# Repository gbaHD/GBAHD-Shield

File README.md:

# gbaHD Shield
This is a shield for the [gbaHD project](https://github.com/zwenergy/gbaHD).  

# What is the gbaHD Shield?
The gbaHD Shield is an easy solution to interface with the Spartan Edge Accelerator Board used for the gbaHD Project and the GBA / GBA-SP itself.

It has the following features.
- Connects via female headers to the Edge board (shield)
- Has a FFC 40 pin connector for OGBA LCD connector. Need Type-B Cable (Reverse) vvv=======^^^
- Has a FFC 32 pin connector for OGBA LCD connector. Need Type-B Cable (Reverse) vvv=======^^^
- Has a FFC 34 pin connector for GBA-SP LCD connector. Need Type-A Cable (Direct) vvv=======vvv
- Has a FFC 16 pin connector for controls with a wire up board. Need Type-B Cable (Reverse) vvv=======^^^
- Has a ATMEGA328p / ATMEGA168p / ATMEGA88p for using a SNES connector to control the GBA.
- Has a high-side switch for GBA power controls (IGR).
- Optional Flex-Cable to solder on the the CPU of the GBA and the GBASP
- Unused ATMEGA-Pins are broken out as testpoints on the top and bottom side for future features.

In cooperation with bbsan the featureset of the Shield has been expanded.
The new features are:
- Update of the ATMEGA Firmwre over the ESP32
- Bluetooth-Controller Support
- WebUI
- OTA-Update of the ESP32, ATMEGA and Bitstreams over the WebUI
- Bitstream selection (720p / 1080p) in the WebUI

## Special Thanks
- @zwenergy0 for the gbaHD-Project itself
- @bbsan2k for all the hard work with the ESP32-Side
- @ManCloud for the Shield design itself
- @jotheripper for the awesome cases (https://www.prusaprinters.org/social/170041-jotheripper/about)
- @ricardoquesada for the BluePad-Implementation (https://github.com/ricardoquesada/bluepad32)

## Contributing
If you wish to contribute, see something wrong or want to add a feature please make a pull request or leave an issue!

## BOM
|Reference	|Value    |
|---------	|--------						|
|C1,C3	|100nF - 0805|
|C2	|22u - 0805|
|C4	|47uF - 0805|
|R1	|2.2k - 0805|
|R2,R7,R6	|1k - 0805|
|R3,R4,R8	|10K - 0805|
|R5	|500 - 0805|
|D1	|LED RED - 0805|
|D2	|LED GREEN - 0805|
|U1	|AZ1117R-ADJ - SOT-89-3|
|U2,U3	|74HC595 - SOIC-16|
|U4	|SNES_7PIN|
|U5	|ATmega328P-AU|
|U5-Alternative	|ATmega168P-AU|
|U5-Alternative-Alternative	|ATmega88PA-AU|
|Q1	|SI2301CDS-T1-GE3 - SOT-23|
|Q2,Q3	|2N7002 - SOT-23|
|SW1	|XKB-TS-1185EC-C-D-B|
|J2			|32Pin 0.5 Pitch, bottom contacts|
|J3			|34Pin 0.5 Pitch, bottom contacts|
|J4			|16Pin 0.5 Pitch, bottom contacts|
|J5			|40Pin 0.5 Pitch, bottom contacts|
|J6	|PinHeader 1x6 2.54mm|
|J7,J9	|PinHeader 1x8 2.54mm|
|J8,J10	|PinHeader 1x10 2.54mm|

## Images

Breakout-Board for the OGBA

Breakout-Board for the GBA-SP

Flex-Cable for the GBA

Flex-Cable for the GBA-SP

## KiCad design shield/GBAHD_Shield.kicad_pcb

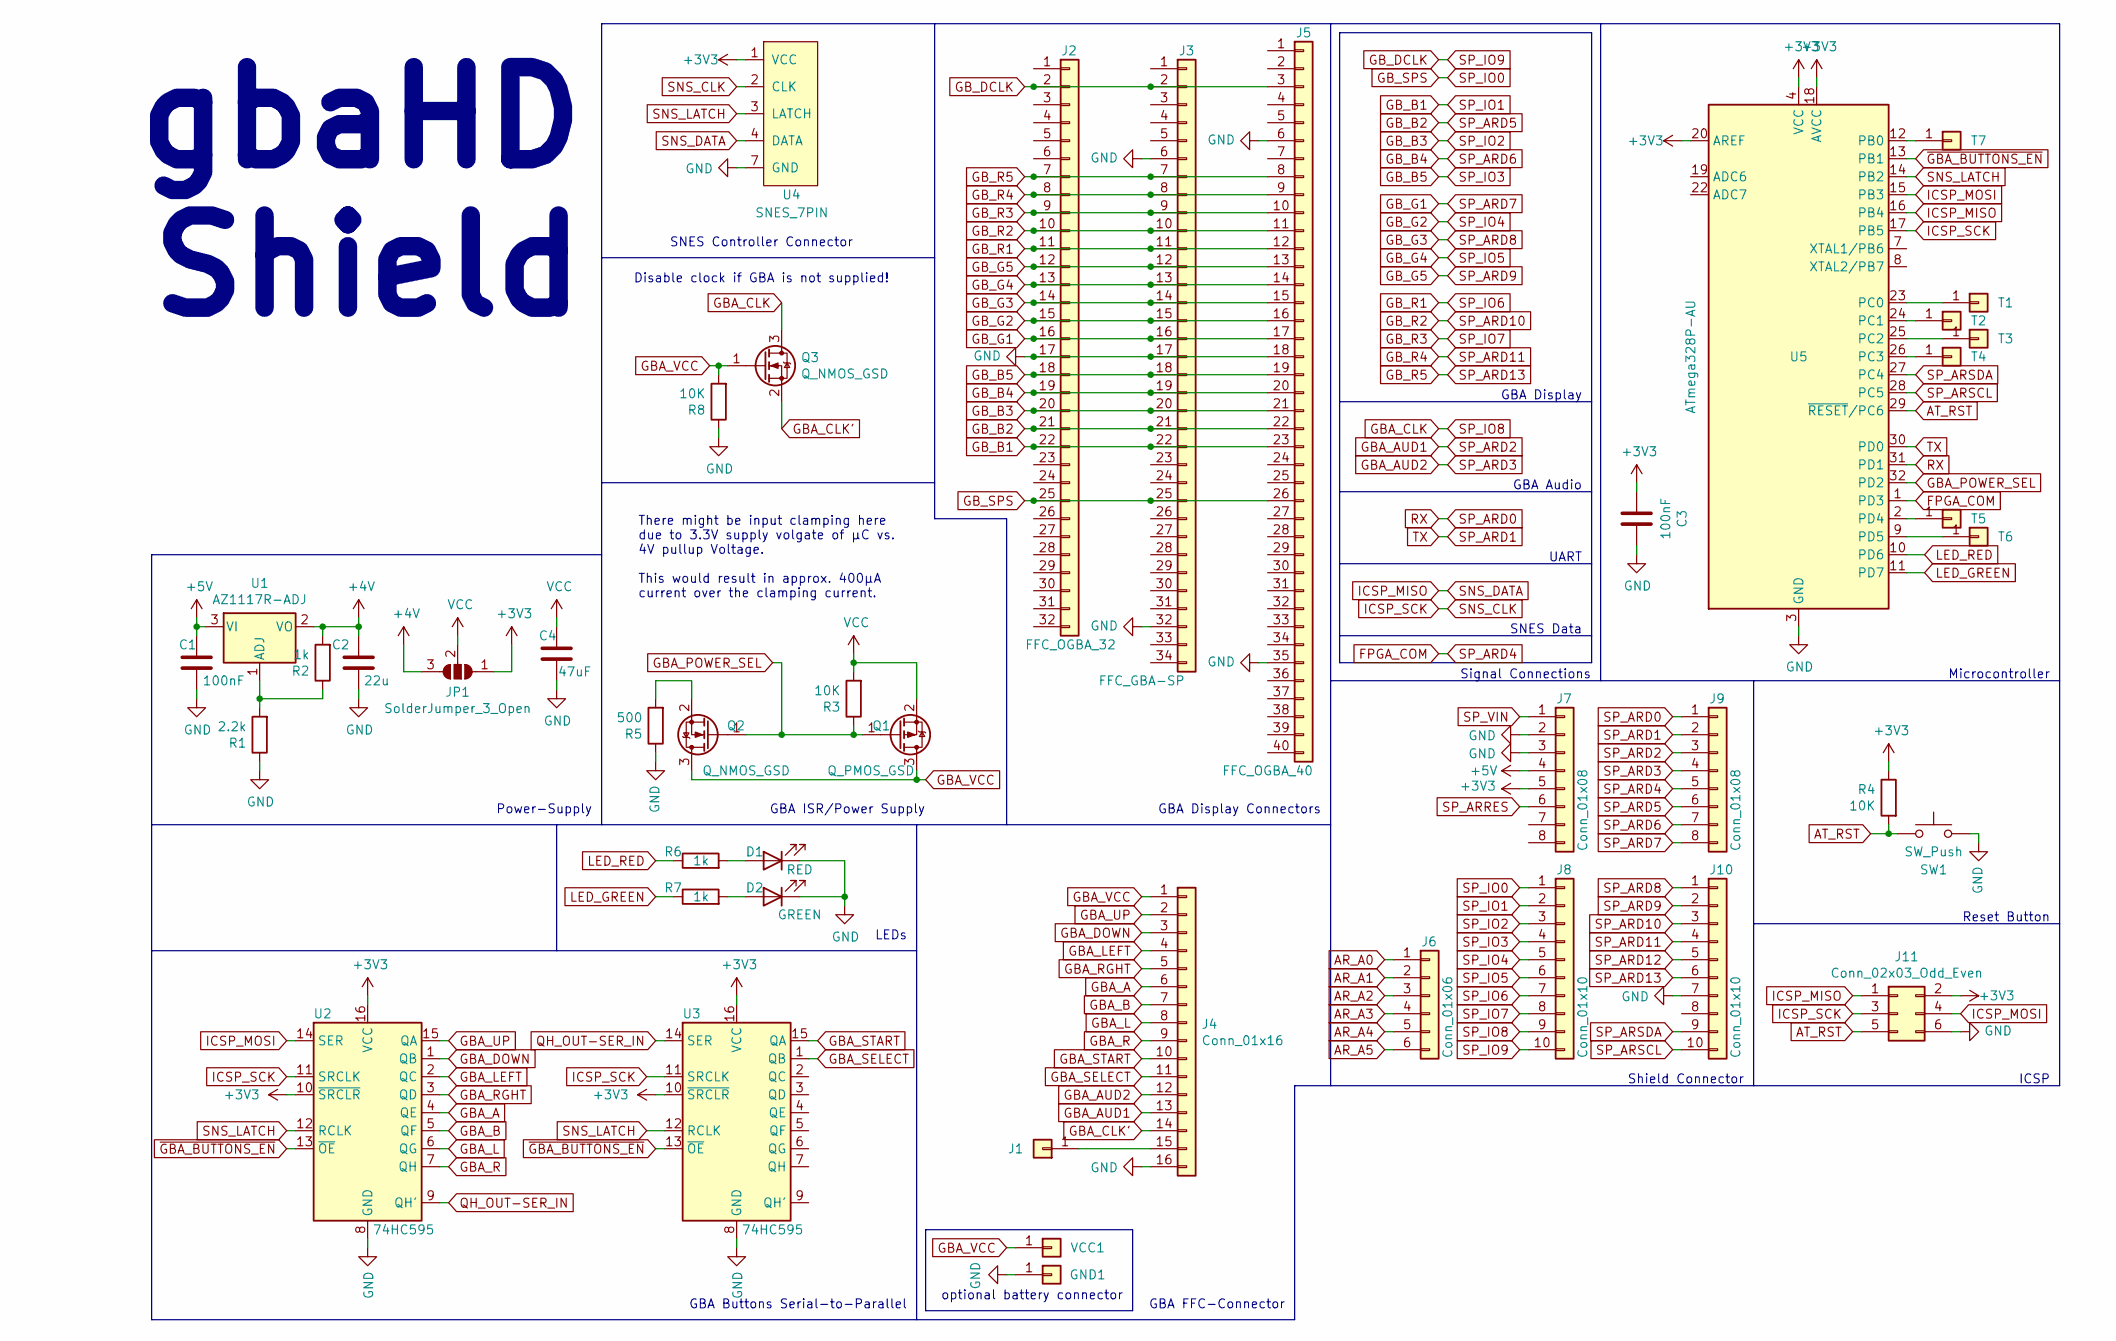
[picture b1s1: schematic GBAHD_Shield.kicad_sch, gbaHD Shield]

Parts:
C1, C3: 100nF; C_0805_2012Metric_Pad1.18x1.45mm_HandSolder
C2: 22u; C_0805_2012Metric_Pad1.18x1.45mm_HandSolder
C4: 47uF; C_0805_2012Metric_Pad1.18x1.45mm_HandSolder
D1: RED; LED_0805_2012Metric_Pad1.15x1.40mm_HandSolder
D2: GREEN; LED_0805_2012Metric_Pad1.15x1.40mm_HandSolder
GND1: Conn_01x01; TestPoint_Pad_1.5x1.5mm
J1: Conn_01x01; TestPoint_Pad_1.5x1.5mm
J2: FFC_OGBA_32; TE_3-1734839-2_1x32-1MP_P0.5mm_Horizontal
J3: FFC_GBA-SP; TE_3-1734839-4_1x34-1MP_P0.5mm_Horizontal
J4: Conn_01x16; TE_1-1734839-6_1x16-1MP_P0.5mm_Horizontal
J5: FFC_OGBA_40; TE_4-1734839-0_1x40-1MP_P0.5mm_Horizontal
J6: Conn_01x06; PinHeader_1x06_P2.54mm_Vertical
J7, J9: Conn_01x08; PinHeader_1x08_P2.54mm_Vertical
J8, J10: Conn_01x10; PinHeader_1x10_P2.54mm_Vertical
J11: Conn_02x03_Odd_Even; PinHeader_2x03_P2.54mm_Vertical
JP1: SolderJumper_3_Open; SolderJumper-3_P1.3mm_Open_Pad1.0x1.5mm_NumberLabels
Q1: Q_PMOS_GSD; SOT-23
Q2, Q3: Q_NMOS_GSD; SOT-23
R1: 2.2k; R_0805_2012Metric_Pad1.20x1.40mm_HandSolder
R2, R6, R7: 1k; R_0805_2012Metric_Pad1.20x1.40mm_HandSolder
R3, R4, R8: 10K; R_0805_2012Metric_Pad1.20x1.40mm_HandSolder
R5: 500; R_0805_2012Metric_Pad1.20x1.40mm_HandSolder
SW1: SW_Push; SW_Push_1P1T_NO_CK_KMR2
T1, T2, T3, T4, T5, T6, T7: Conn_01x01; TestPoint_Pad_D1.5mm
U1: AZ1117R-ADJ; SOT-89-3
U2, U3: 74HC595; SOIC-16_3.9x9.9mm_P1.27mm
U4: SNES_7PIN
U5: ATmega328P-AU; TQFP-32_7x7mm_P0.8mm
VCC1: Conn_01x01; TestPoint_Pad_1.5x1.5mm

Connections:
+3V3: C3.2, J7.5, J11.2, JP1.1 (A), R4.1, U2.10 (~SRCLR), U2.16 (VCC), U3.10 (~SRCLR), U3.16 (VCC), U4.1 (VCC), U5.4 (VCC), U5.6 (VCC), U5.18 (AVCC), U5.20 (AREF)
+4V: C2.2, JP1.3 (B), R2.2, U1.2 (VO)
+5V: C1.2, J7.4, U1.3 (VI)
AR_A0: J6.1
AR_A1: J6.2
AR_A2: J6.3
AR_A3: J6.4
AR_A4: J6.5
AR_A5: J6.6
AT_RST: J11.5, R4.2, SW1.1, U5.29 (~RESET/PC6)
FPGA_COM: J9.5, U5.1 (PD3)
GBA_A: J4.6, U2.4 (QE)
GBA_AUD1: J4.13, J9.3
GBA_AUD2: J4.12, J9.4
GBA_B: J4.7, U2.5 (QF)
GBA_CLK: J8.9, Q3.3 (D)
GBA_CLK': J4.14, Q3.2 (S)
GBA_DOWN: J4.3, U2.1 (QB)
GBA_L: J4.8, U2.6 (QG)
GBA_LEFT: J4.4, U2.2 (QC)
GBA_POWER_SEL: Q1.1 (G), Q2.1 (G), R3.1, U5.32 (PD2)
GBA_R: J4.9, U2.7 (QH)
GBA_RGHT: J4.5, U2.3 (QD)
GBA_SELECT: J4.11, U3.1 (QB)
GBA_START: J4.10, U3.15 (QA)
GBA_UP: J4.2, U2.15 (QA)
GBA_VCC: J4.1, Q1.3 (D), Q2.3 (D), Q3.1 (G), R8.2, VCC1.1
GB_B1: J2.22, J3.22, J5.23, J8.2
GB_B2: J2.21, J3.21, J5.22, J9.6
GB_B3: J2.20, J3.20, J5.21, J8.3
GB_B4: J2.19, J3.19, J5.20, J9.7
GB_B5: J2.18, J3.18, J5.19, J8.4
GB_DCLK: J2.2, J3.2, J5.3, J8.10
GB_G1: J2.16, J3.16, J5.17, J9.8
GB_G2: J2.15, J3.15, J5.16, J8.5
GB_G3: J2.14, J3.14, J5.15, J10.1
GB_G4: J2.13, J3.13, J5.14, J8.6
GB_G5: J2.12, J3.12, J5.13, J10.2
GB_R1: J2.11, J3.11, J5.12, J8.7
GB_R2: J2.10, J3.10, J5.11, J10.3
GB_R3: J2.9, J3.9, J5.10, J8.8
GB_R4: J2.8, J3.8, J5.9, J10.4
GB_R5: J2.7, J3.7, J5.8, J10.6
GB_SPS: J2.25, J3.25, J5.26, J8.1
GND: C1.1, C2.1, C3.1, C4.1, D1.1 (K), D2.1 (K), GND1.1, J2.17, J3.6, J3.17, J3.32, J4.16, J5.6, J5.18, J5.35, J7.2, J7.3, J10.7, J11.6, R1.1, R5.1, R8.1, SW1.2, U2.8 (GND), U3.8 (GND), U4.7 (GND), U5.3 (GND), U5.5 (GND), U5.21 (GND)
ICSP_MISO: J11.1, U4.4 (DATA), U5.16 (PB4)
ICSP_MOSI: J11.4, U2.14 (SER), U5.15 (PB3)
ICSP_SCK: J11.3, U2.11 (SRCLK), U3.11 (SRCLK), U4.2 (CLK), U5.17 (PB5)
LED_GREEN: R7.1, U5.11 (PD7)
LED_RED: R6.1, U5.10 (PD6)
unnamed: D1.2 (A), R6.2
unnamed: D2.2 (A), R7.2
unnamed: J1.1, J4.15
unnamed: Q2.2 (S), R5.2
unnamed: R1.2, R2.1, U1.1 (ADJ)
unnamed: T1.1, U5.23 (PC0)
unnamed: T2.1, U5.24 (PC1)
unnamed: T3.1, U5.25 (PC2)
unnamed: T4.1, U5.26 (PC3)
unnamed: T5.1, U5.2 (PD4)
unnamed: T6.1, U5.9 (PD5)
unnamed: T7.1, U5.12 (PB0)
QH_OUT-SER_IN: U2.9 (QH'), U3.14 (SER)
RX: J9.1, U5.31 (PD1)
SNS_LATCH: U2.12 (RCLK), U3.12 (RCLK), U4.3 (LATCH), U5.14 (PB2)
SP_ARD1: J9.2, U5.30 (PD0)
SP_ARD12: J10.5
SP_ARRES: J7.6
SP_ARSCL: J10.10, U5.28 (PC5)
SP_ARSDA: J10.9, U5.27 (PC4)
SP_VIN: J7.1
VCC: C4.2, JP1.2 (C), Q1.2 (S), R3.2
~GBA_BUTTONS_EN: U2.13 (~OE), U3.13 (~OE), U5.13 (PB1)

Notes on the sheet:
ICSP
GBA Buttons Serial-to-Parallel
GBA FFC-Connector
GBA ISR/Power Supply
SNES Data
optional battery connector
There might be input clamping here due to 3.3V supply volgate of µC vs. 4V pullup Voltage. This would result in approx. 400µA current over the clamping current.
Microcontroller
GBA Display Connectors
Shield Connector
gbaHD Shield
UART
LEDs
Power-Supply
Disable clock if GBA is not supplied!
SNES Controller Connector
Reset Button
Signal Connections
GBA Display
GBA Audio

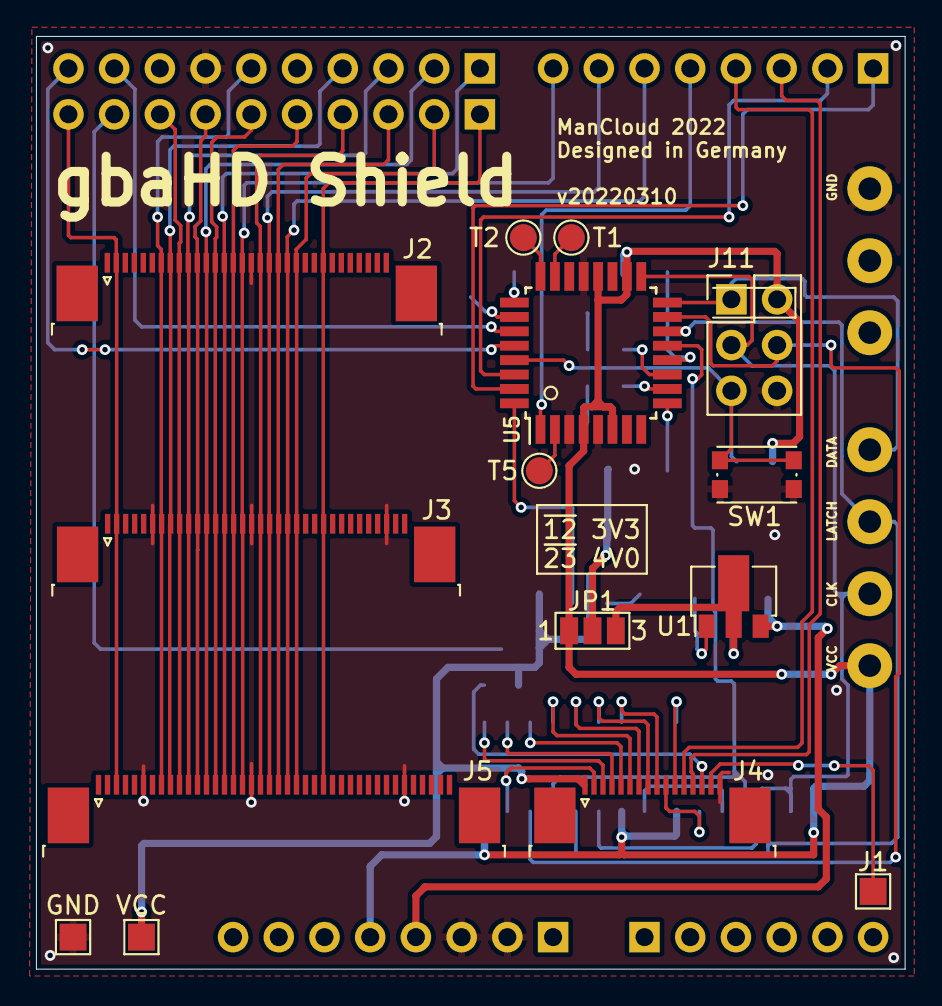
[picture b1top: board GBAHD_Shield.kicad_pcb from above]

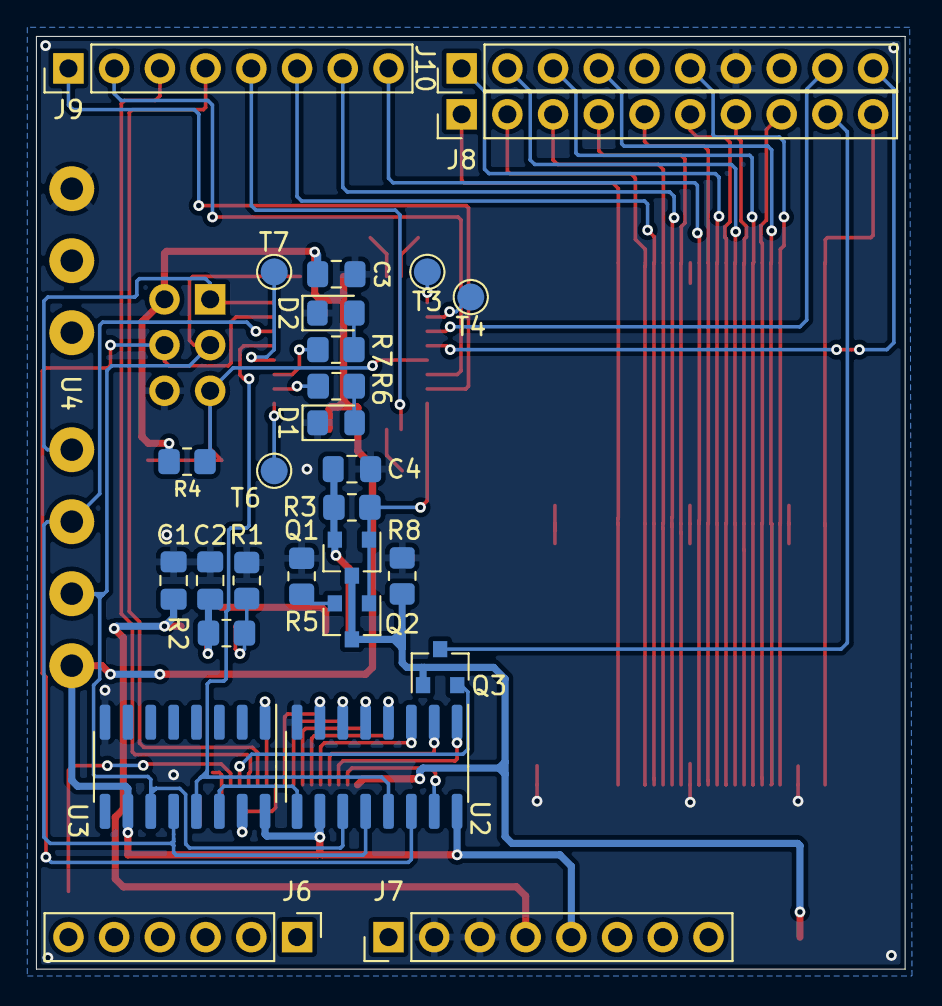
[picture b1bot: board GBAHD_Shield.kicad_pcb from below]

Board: 2 copper layers, 48.3 x 51.8 mm, 44 parts (29 on the bottom side), 64 nets.

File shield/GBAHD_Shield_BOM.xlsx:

ID | Part | Outline | Qty. | Value | Reference | LCSC Part Number | Note
1 | C1,C3 | C_0805_2012Metric_Pad1.18x1.45mm_HandSolder | 2 | 100nF |  | C519981
2 | C2 | C_0805_2012Metric_Pad1.18x1.45mm_HandSolder | 1 | 22u |  | C109314
3 | J11 | PinHeader_2x03_P2.54mm_Vertical | 1 | Conn_02x03_Odd_Even |  | C65114
4 | J2 | TE_3-1734839-2_1x32-1MP_P0.5mm_Horizontal | 1 | FFC_OGBA_32 | JUSHUO AFC07-S32FCC-00 | C11061
5 | J3 | TE_3-1734839-4_1x34-1MP_P0.5mm_Horizontal | 1 | FFC_GBA-SP | JUSHUO AFC07-S34FCC-00 | C262221
6 | J4 | TE_1-1734839-6_1x16-1MP_P0.5mm_Horizontal | 1 | Conn_01x16 | JUSHUO AFC07-S16FCC-00 | C11053
7 | J5 | TE_4-1734839-0_1x40-1MP_P0.5mm_Horizontal | 1 | FFC_OGBA_40 | JUSHUO AFC07-S40FCC-00 | C11062
8 | J6 | PinHeader_1x06_P2.54mm_Vertical | 1 | Conn_01x06 |  | C40877
9 | J8,J10 | PinHeader_1x10_P2.54mm_Vertical | 2 | Conn_01x10 |  | C35445
10 | J9,J7 | PinHeader_1x08_P2.54mm_Vertical | 2 | Conn_01x08 |  | C27438
11 | Q1 | SOT-23 | 1 | Q_PMOS_GSD | SI2301DS | C10487
12 | R1 | R_0805_2012Metric_Pad1.20x1.40mm_HandSolder | 1 | 2.2k |  | C228697
13 | R2 | R_0805_2012Metric_Pad1.20x1.40mm_HandSolder | 1 | 1k |  | C140870
14 | R4,R3 | R_0805_2012Metric_Pad1.20x1.40mm_HandSolder | 2 | 10K |  | C84376
15 | SW1 | SW_Push_1P1T_NO_CK_KMR2 | 1 | SW_Push | TS-1185EC-C-D-B | C318893
16 | U1 | SOT-89-3 | 1 | LM1117F-ADJ |  | C126021
17 | U2,U3 | SOIC-16_3.9x9.9mm_P1.27mm | 2 | 74HC595 |  | C5947
18 | U4 | SNES_7PIN | 1 | SNES_7PIN |  |  | Available on aliexpress - make sure you choose the right angle one (180 degrees) | https://de.aliexpress.com/item/32828768824.html?spm=a2g0o.pr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
19 | U5 | TQFP-32_7x7mm_P0.8mm | 1 | ATmega328P-AU |  | C14877
20 |  |  | 2 |  | Pin Headers 1*40 Pin |  | Available on aliexpress - make sure you choose the right angle one (180 degrees) | https://de.aliexpress.com/item/32993182990.html?spm=a2g0o.pr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
 |  | Flexcable 40 Pin | 1 |  | 0.020"(0.50mm) 40 Opposite Side FFC/FPC Connectors RoHS | C11100 | The flex is a bit long, but you can fold it to fit. LCSC has no shorter ones
 |  | Flexcable 16 Pin | 1 |  | 0.020"(0.50mm) 16 Opposite Side FFC/FPC Connectors RoHS | C11114 | The flex is a bit long, but you can fold it to fit. LCSC has no shorter ones
 |  | Flexcable 32 Pin | 1 |  | 0.020"(0.50mm) 32 Opposite Side FFC/FPC Connectors RoHS | C11118 | The flex is a bit long, but you can fold it to fit. LCSC has no shorter ones
 |  | Flexcable 34 Pin | 1 |  | 0.020"(0.50mm) 32 Same Side FFC/FPC Connectors RoHS |  | Not available on LCSC, try ordering on ebay, aliexpress e.g. | https://de.aliexpress.com/item/1005002259855390.html?spm=a2g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

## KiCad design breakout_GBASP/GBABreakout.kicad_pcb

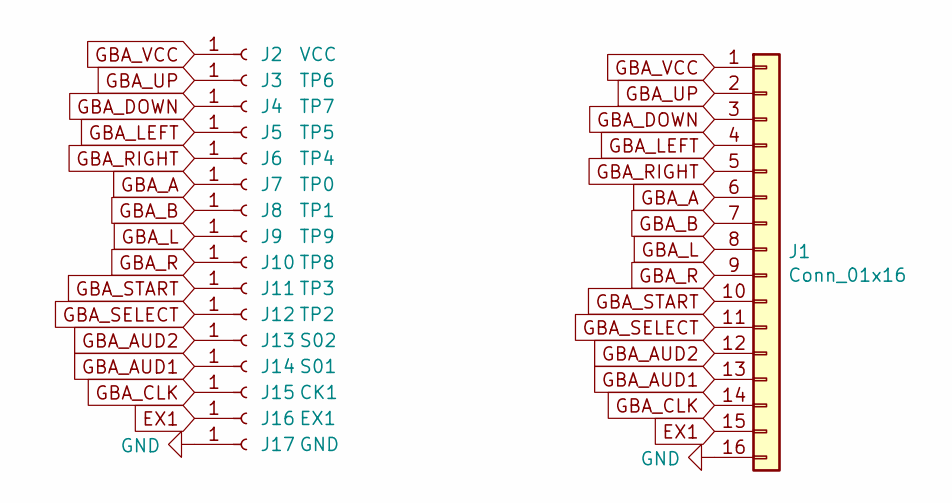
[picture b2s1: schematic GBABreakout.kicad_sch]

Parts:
J1: Conn_01x16; TE_1-1734839-6_1x16-1MP_P0.5mm_Horizontal
J2: VCC; SOLDER_PAD
J3: TP6; SOLDER_PAD
J4: TP7; SOLDER_PAD
J5: TP5; SOLDER_PAD
J6: TP4; SOLDER_PAD
J7: TP0; SOLDER_PAD
J8: TP1; SOLDER_PAD
J9: TP9; SOLDER_PAD
J10: TP8; SOLDER_PAD
J11: TP3; SOLDER_PAD
J12: TP2; SOLDER_PAD
J13: S02; SOLDER_PAD
J14: S01; SOLDER_PAD
J15: CK1; SOLDER_PAD
J16: EX1; SOLDER_PAD
J17: GND; SOLDER_PAD

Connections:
EX1: J1.15, J16.1
GBA_A: J1.6, J7.1
GBA_AUD1: J1.13, J14.1
GBA_AUD2: J1.12, J13.1
GBA_B: J1.7, J8.1
GBA_CLK: J1.14, J15.1
GBA_DOWN: J1.3, J4.1
GBA_L: J1.8, J9.1
GBA_LEFT: J1.4, J5.1
GBA_R: J1.9, J10.1
GBA_RIGHT: J1.5, J6.1
GBA_SELECT: J1.11, J12.1
GBA_START: J1.10, J11.1
GBA_UP: J1.2, J3.1
GBA_VCC: J1.1, J2.1
GND: J1.16, J17.1

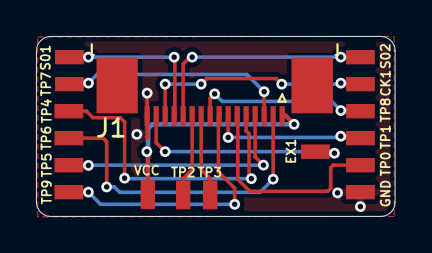
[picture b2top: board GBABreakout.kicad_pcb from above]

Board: 2 copper layers, 19.9 x 10.0 mm, 17 parts (0 on the bottom side), 16 nets.

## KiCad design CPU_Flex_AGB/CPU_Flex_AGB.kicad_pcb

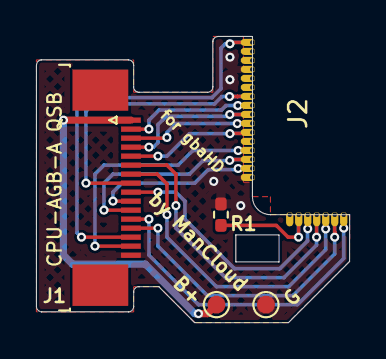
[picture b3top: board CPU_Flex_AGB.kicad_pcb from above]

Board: 2 copper layers, 17.4 x 15.9 mm, 5 parts (0 on the bottom side), 17 nets.

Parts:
B+: BAT+; TestPoint_Pad_D1.0mm
G: GND; TestPoint_Pad_D1.0mm
J1: Conn_01x16; TE_1-1734839-6_1x16-1MP_P0.5mm_Horizontal
J2: CPU_AGB_A_Interface; CPU_AGB_A_INTERFACE
R1: 100k; R_0402_1005Metric_Pad0.72x0.64mm_HandSolder

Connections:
GND: G.1, J1.16, J2.116 (GND), J2.128 (GND), R1.1
unnamed: J1.2, J2.120 (TP6)
unnamed: J1.3, J2.122 (TP7)
unnamed: J1.4, J2.121 (TP5)
unnamed: J1.5, J2.123 (TP4)
unnamed: J1.6, J2.4 (TP0)
unnamed: J1.7, J2.5 (TP1)
unnamed: J1.8, J2.119 (TP9)
unnamed: J1.9, J2.3 (TP8)
unnamed: J1.10, J2.127 (TP3)
unnamed: J1.11, J2.126 (TP2)
unnamed: J1.12, J2.7 (S02)
unnamed: J1.13, J2.6 (S01)
unnamed: J1.14, J2.113 (CK1)
unnamed: J1.15, J2.125 (RESET)
unnamed: J2.2 (IN35), R1.2
VCC: B+.1, J1.1

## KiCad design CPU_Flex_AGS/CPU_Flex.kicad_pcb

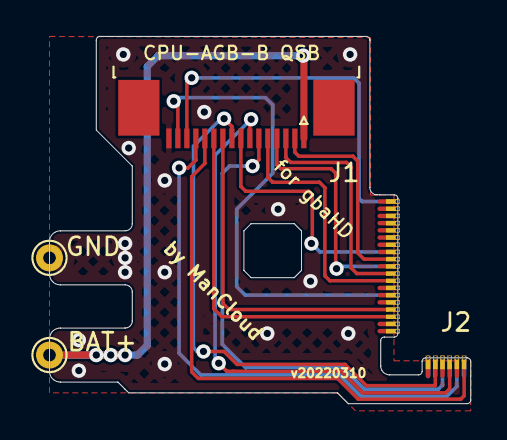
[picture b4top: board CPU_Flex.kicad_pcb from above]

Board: 2 copper layers, 23.4 x 20.4 mm, 4 parts (0 on the bottom side), 16 nets.

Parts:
BAT+: Conn_01x01; TestPoint_THTPad_D1.5mm_Drill0.7mm
GND: Conn_01x01; TestPoint_THTPad_D1.5mm_Drill0.7mm
J1: Conn_01x16; TE_1-1734839-6_1x16-1MP_P0.5mm_Horizontal
J2: CPU AGB B Interface; CPU_AGB_B_Interface

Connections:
/GBA_A: J1.6, J2.3 (TP0)
/GBA_AUD_L: J1.12, J2.6 (S02)
/GBA_AUD_R: J1.13, J2.5 (S01)
/GBA_B: J1.7, J2.4 (TP1)
/GBA_CLK: J1.14, J2.138 (CK1)
/GBA_DOWN: J1.3, J2.148 (TP7)
/GBA_L: J1.8, J2.145 (TP9)
/GBA_LEFT: J1.4, J2.147 (TP5)
/GBA_R: J1.9, J2.2 (TP8)
/GBA_RESET: J1.15, J2.151 (RESET)
/GBA_RIGHT: J1.5, J2.149 (TP4)
/GBA_SELECT: J1.11, J2.154 (TP2)
/GBA_START: J1.10, J2.153 (TP3)
/GBA_UP: J1.2, J2.146 (TP6)
GND: GND.1, J1.16
VCC: BAT+.1, J1.1

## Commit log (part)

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2021-05-11 pictures for wiki
2021-05-18 Add files via upload
    1K res between Bat- and Bat+
2021-06-12 changed IGR combo, added filter restore combo, fixed no-controller handling
2021-06-13 sp-case pictures
    sp-case pictures
2021-06-13 ogba wiki
    ogba wiki
2021-06-13 ogba_case
2021-06-26 spartan_with_headers
2021-07-11 Update README.md
    Fixed wrong part case for U2,U3
2021-07-19 2nd case-pictures
2021-07-19 added OSD-control interface
    activate OSD: L + R + SELECT + UP
    deactivate ODS: START
2021-11-09 updated shield
2021-11-09 added twiboot submodule
2021-11-09 update submodules
2021-11-09 added EPS32 testcode for Bootloader
2021-11-10 compressed images
2021-12-14 Added submodules for arduino as a component and Bluepad32
2021-12-14 Added build scripts
2021-12-14 Add build folder to gitignore
2021-12-14 Add source template
2021-12-14 Ignore generated components
2021-12-14 Remove get_components from Makefile, fix bluepad path
2021-12-14 Fixed naming of submodule
2021-12-14 Fixed submodule mess
2021-12-14 Removed bluepad32
2021-12-14 Re-Add Bluepad32 properly
2021-12-14 Update Build for adding web/bitstream handler
2021-12-14 Add implementation for web handler and bitstream handler
2021-12-16 Update arduino version
2021-12-18 Fix build by using bluepad template as component foundation
2021-12-18 Removed bluepad submodule
2021-12-18 Copying default component files
2021-12-18 Remove get_components
2021-12-21 Improved over all build config
2021-12-21 Overall refactoring and added wifi and mega handler
2021-12-21 Minor updates to sdkconfig
2021-12-22 Add first crude version to update firmware
2021-12-22 Remove Bluepad Debug outputs
2021-12-22 some cleanup
2021-12-22 updated .gitignore and added some files
2021-12-22 updated gitmodules
2021-12-22 fixed submodules
2021-12-23 Update Upgrade function
2021-12-23 Fix gitignore
2021-12-23 Fix SPIFFS upload
2021-12-24 a little bit of tinkering
2021-12-24 Changed order of run/init to be faster for TWI
2021-12-24 Removed endTransmission after requestFrom
2021-12-24 changed twi handling
2021-12-24 added definition for bigger I2C-Buffer
2021-12-25 remove wifi
2021-12-25 Fix sending of inputs without controller available
2021-12-25 Fix WiFi
2021-12-25 fixed button mapping
2021-12-25 fixed button mappings and polling intervalls
2021-12-26 Improve Timer Code
2021-12-28 Refactoring and Preferences
2021-12-28 Add Prefs
2021-12-28 fixed verify_flash() --> missing beginTransmission()
2021-12-31 Added Bluetooth Mapping, Preferences Refactoring
2021-12-31 Add bluetooth cfg
2021-12-31 Refactoring
2021-12-31 Remove template
2021-12-31 CMake fixes
2021-12-31 changed TWI handling - added data validity timeout
2022-01-01 Added License Hadder
2022-01-02 updated CPU-flex
2022-01-03 Beautifying
2022-01-03 Update Bitstream
2022-01-03 refactored avr-firmware to be makefile project
2022-01-03 added controller detection
2022-01-04 Better layout
2022-01-04 Better shield handling
2022-01-04 Better OTA
2022-01-09 For now - only load bitstream from SPIFFS to be faster
2022-01-09 Add Force option for ATMega update
2022-01-09 Added Force Option for Mega Update
2022-01-09 Update to latest version
2022-01-09 Update Web files
2022-01-09 Build folder
2022-01-15 New Bluepad32 version
2022-01-15 Fix arduino build with new bluepad version
2022-01-15 New Bluepad version fixes
2022-01-15 Add Bluetooth Enable/Disable, Make communication stateful
2022-01-16 Make Bitstream selectable
2022-01-16 Fix Preferences
2022-01-16 Refactor index
2022-01-16 Fix ESP-IDF CI(?)
2022-01-16 added TWI_flush(), reading the buffer does no longer lears the buffer
2022-01-16 added bt_controller connected flag
2022-01-16 updated twi polling to not use delays but "connected flags" instead
2022-01-16 Fix BT Available
2022-01-18 Submodules
2022-01-18 Use IDF 4.4
2022-01-18 Artifacts
2022-01-18 Auto Release Draft
2022-01-28 Add new ATMega version
2022-01-28 Refactor settings
2022-01-28 Fix Wrong CTRLs and Controller flickering
2022-01-28 Refactor for readability
2022-01-28 Fix 1080p Path
2022-01-28 Save and Reboot
2022-01-28 Try to improve WiFi
2022-01-28 updated twi-data handling
2022-01-31 Add copying latest bitstream
2022-01-31 Add submodule for zwenergys repo
2022-02-11 Added submodules
2022-02-11 Major Update containing: - LittleFS replaces SPIFFS - ESPAsyncWebserver - WebSerial - First OTA steps
2022-02-14 Update BluePad
2022-02-14 Add Log Handler
2022-02-14 WiFI Max Power
2022-02-14 Fix issues with stuck updates
2022-02-14 Fix SDK Config
2022-02-14 Temporarily Change arduino submodule
2022-02-14 Set Arduino to correct commit
2022-02-14 Change Release plugin
2022-02-14 Fix Usage of BTStack
2022-02-14 Fix old CMake compatibility
2022-02-14 Add AVR build
2022-02-14 Fix avr build
2022-02-14 Add avr-gcc to path
2022-02-14 Update atmega binary in LittleFS/SPIFFS partition
2022-02-14 Collect files
2022-02-14 Fix issue when pulling
2022-02-14 Fix in proper git
2022-02-14 Do not update submodule for now
2022-02-14 Proper Release naming
2022-02-14 release all bins from /tmp/release
2022-02-18 Add release name
2022-02-18 Commit new ATMega Build
2022-02-18 Check in at proper location
2022-02-18 Update to latest Bitstream
2022-02-18 make clean
2022-02-18 Workaround
2022-02-18 Fix commits
2022-02-19 Rename action
2022-02-19 Use Add and Commit
2022-02-19 Remoev default author
2022-02-19 Remove ATMega stuff
2022-02-19 GTrack change with empty base
2022-02-19 Use proper var
2022-02-19 Another fix
2022-02-19 Fix Change detection
2022-02-20 Better release versioning
2022-02-20 Fetch all tags
2022-02-20 Fetch origin
2022-02-20 Fetch during checkout
2022-02-22 Fix Arduino Repo
2022-02-25 Publish release instead of prerelease
2022-02-25 Fix Stuck OTA
2022-02-25 Set Bitstream URL back to zwenergy
2022-02-25 Call clear instead of setting string to ""
2022-02-25 Add Bitstream Version identification
2022-02-25 Remove old OTA call
2022-02-25 Don't copy Bitstream at Build Time
2022-02-25 Fix Version naming
2022-02-28 Fix Heap Overflow
2022-02-28 Fix WDT most of the times
2022-02-28 Remove Logging BS Version
2022-02-28 Add Token to Preferences for "testing" channel
2022-02-28 Improve OTA code
2022-02-28 Fix crash and changelog
2022-02-28 Fix noop
2022-02-28 Re Enable Bitstream pushing
2022-02-28 Updated QSB for AGB/AGS CPU
2022-02-28 updated PCB - reorganized file structure
2022-02-28 updated modules
2022-02-28 Updated files to KiCad6
2022-02-28 removed outdated files
2022-02-28 updated reference to twiboot
2022-03-01 Remove Debug Output
2022-03-01 Fix non present FPGA on dev board
2022-03-01 Fix Update Check
2022-03-01 Fix Types
2022-03-01 Exclude latest tag for release description
2022-03-01 Build TWIBoot
2022-03-01 Fix line
2022-03-01 Fix(?)
2022-03-01 Fix(!)
2022-03-02 Fix issue in spiffs upload
2022-03-02 Hopefully fix changed flag
2022-03-02 Run Hourly
2022-03-04 Remove base from PathFilter for now
2022-03-05 Fix Navigation and Stuck Update
2022-03-05 Fix Workflow: Use new checkout and don't do pre-release
2022-03-06 Update Logo
2022-03-06 Add Update Fallback
2022-03-06 Add README
2022-03-06 More release artifacts
2022-03-06 Fix README
2022-03-06 Fix Logo
2022-03-06 Cleanup
2022-03-06 Fix workflow
2022-03-06 Fix underscore
2022-03-06 Next try
2022-03-06 cp - not co
2022-03-07 Another try...
2022-03-07 remove unshallow
2022-03-07 Show git describe
2022-03-07 Show Version string
2022-03-07 Without release tag
2022-03-07 Try to fix release
2022-03-07 Improve WebIf based on jotherippers suggestions
2022-03-07 Fix SD Card (?)
2022-03-07 Fix esp32 ota
2022-03-07 Fix SD Card Update
2022-03-08 get newest bit stream at every run/build
2022-03-08 Fix correct pull
2022-03-08 Ignore bitstreams as they will be added during build
2022-03-08 Add correct names
2022-03-08 Change WiFi config File
2022-03-08 Optical fixes
2022-03-09 Add CSS Fix from joTheRipper
2022-03-09 Add new css
2022-03-09 Fix Changelog displaying
2022-03-12 Fix initial pairing, forget keys at startup
2022-03-12 Remove manual bitstream update for now
2022-03-12 Remove forget Keys again
2022-03-12 Set Max Gamepads to 2 in Bluepad again
2022-03-12 Update BluePad32
2022-03-12 Link in new tab in OTA view
2022-03-12 Output Controller Name
2022-03-12 Cosmetics
2022-03-12 Name debugging
2022-03-13 Changed SPI Mode
2022-03-13 updated twiboot-module
2022-03-13 Updated PCBs
2022-03-13 Add Forget all BT Devices
2022-03-13 Fix path filter
2022-03-13 Fix branch
2022-03-13 Remove filter base
2022-03-13 Fix TWIBoot build
2022-03-14 Cosmetics in webif
2022-03-14 Update BluePad to latest version
2022-03-14 Fix Reset Shield Once and for All!
2022-03-14 Develop (#16)
    * Remove get_components from Makefile, fix bluepad path
    * Fixed naming of submodule
    * Fixed submodule mess
    * Removed bluepad32
    * Re-Add Bluepad32 properly
    * Update Build for adding web/bitstream handler
2022-03-14 Use also lightweight tags
2022-03-15 Fix X and Y Mapping
2022-03-16 updated shield production files
2022-03-16 added AGS-Flex-QSB production files
2022-03-16 added AGB-Flex-QSB production files
2022-03-16 Delete
2022-03-16 Build TWI and ATMega App here as well
    Fix #17
2022-03-16 Fix path
2022-03-16 Fix Paths again
2022-03-16 Remove dedicated Build action for atmega
2022-03-19 Better OTA failed handling
2022-03-19 Remove WiFi Sleep
2022-03-19 rebuilt the gnd-plane as there was a bridge
2022-03-19 Fix FPGA Push speed
2022-03-21 Initialize Update Structs
2022-03-22 Fix Changelog and Array overflow
2022-03-22 Fix Update Displaying when refresh
2022-03-23 Fix BluePad Config
2022-03-25 Force Update on manual avr.bin Update
2022-03-25 Add Hostname Setting
2022-03-26 - Fix Github Action - Fix Bluepad config - Enhance OTA View - Speedup FPGA Loading - Fix Changelog - Fix Buttonmapping for X / Y - Add hostname to wifi config - Force shield update with offline update
2022-04-21 added support for Consoles4You board
2022-04-22 DEBUG
2022-04-22 Add Serial Input config for Wifi
2022-04-22 fixed watchdog-bug
2022-04-22 fixed pin initialization
2022-05-19 Update Arduino framework
2022-05-19 Update SDK Config
2022-05-19 Minor CSS fixes
2022-05-19 More debug outputs
2022-05-19 Fix FPGA loading for new arduino
2022-05-19 Fix Logging
2022-05-19 Remove call for setting wifi strength
2022-05-19 USe idf 4.4.1 for build
2022-09-26 Fix URLs
2022-09-26 Add Shutdown command to wifi
2022-09-26 Track WS access and shutdown if required
2022-09-26 Add IF to check if OTA is running
2022-09-26 Reset watchdog during upload
2022-09-26 Reset watchdog when pushing bitstream
2022-09-26 tweak config
2022-09-26 Fix Build with new BP32 Dependencies
2022-09-26 Fix Config
2022-09-26 Update ignore
2022-09-26 Add KP Workaround
2022-09-26 Remove Output of free Heap
2022-09-26 Bump IDF to 4.4.2
2022-09-27 Avr aio (#23)
    * fixed watchdog-bug
    * fixed pin initialization
    Authored-by: ManCloud <ch_ruecker@t-online.de>
2022-09-29 Removed old template
2022-09-29 Remove bluepad template
2022-09-29 Use latest idf workflow
2022-09-29 - Fix sudden reboots - Add support for more controllers (update BluePad32 to 3.5.1) - Add support for Consoles4You gbaHD shields
2022-10-30 activated PullUp on MISO
2022-12-05 Fix C4You Shield Compatibility
2023-04-03 Fixed Pull-Up on C4Y gbaHD_US
2023-04-04 Fix C4Y Shield - for real this time
2023-04-04 Dummy change
2023-08-05 Remove WiFi disabler, upgrade to latest versions
2023-08-05 Bump idf to 4.4.5
2023-08-06 Remove Shutdown of WiFi
2023-12-22 Implemented Settings persistency and new OSD approach
2023-12-27 Fix WiFi issues related to ESP Update
2023-12-27 Bump IDF CI version
2023-12-27 Revert Bluepad
2023-12-27 - Update AVR binary for OSD settings persistency - Update IDF to 4.4.6
2024-01-29 Re-Introduce WiFi timeout hack
2024-01-30 Re-introduce WiFi Timeout
2024-01-30 Fix Shutdown Loop
